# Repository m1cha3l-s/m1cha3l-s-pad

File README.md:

# m1cha3l's pad

My take on a macropad but with comfort added. Featuring 4x custom mapable MX-Style switches, 1x Rotary encoder and a 0.91 inch OLED display.

The pad runs KMK Firmware on a Seeed XIAO RP2040. For easy configuration it has been done with POG Configurator for easy setup and reconfiguration. QMK firmware will come in the future to make use of the OLED display.

The current firmware can be found in the m1cha3l folder

# IMPORTANT NOTES

You need to have CircuitPython installed on your board. [Here](https://learn.adafruit.com/welcome-to-circuitpython/installing-circuitpython)'s a guide. After you put the insides of m1cha3l in production or m1cha3l onto the board, or you use [POG](https://pog.heaper.de) to flash and customize.

As of right now the leds and OLED are not yet set up and firmware not yet 100% tested as I don't have the hardware, once I get it I will update it.

To balance the weight you HAVE to put few washers in the bottom part and secure them with hot glue.

You first have to put the switches in the top part, then solder the OLED to the PCB, then you can solder the switches and click them into the bottom part of the case.

The rotary encoder isn't mounted on the PCB due to size savings and also because I wanted to try something new. You can connect it with female jumper cable through the header on the back of the PCB. Also it doesn't have a cap on because I dont like the feeling of them and something just makes me happy seeing raw hardware.

# Looks of the pad

# CAD (Case)

The case uses a screwless design.

# Schematic/PCB

# Hardware used

| Part Name | Quantity |
|---|---:|
| 3D Printed case | 1 |
| Seeed XIAO RP2040 | 1 |
| EC11 Rotary encoders | 1 |
| MX-Style Switch | 4 |
| Keycap | 4 |
| SK6812MINI-E | 4 |
| Custom PCB | 1 |
| Old/washers | 4 |

# My feelings

Love the project from start to finish and it helped me learn a lot of things and guide me to get my first shipped project! I highly suggest you try and build the macropad from scratch yourself as it is easy to understand and teaches you the basics.

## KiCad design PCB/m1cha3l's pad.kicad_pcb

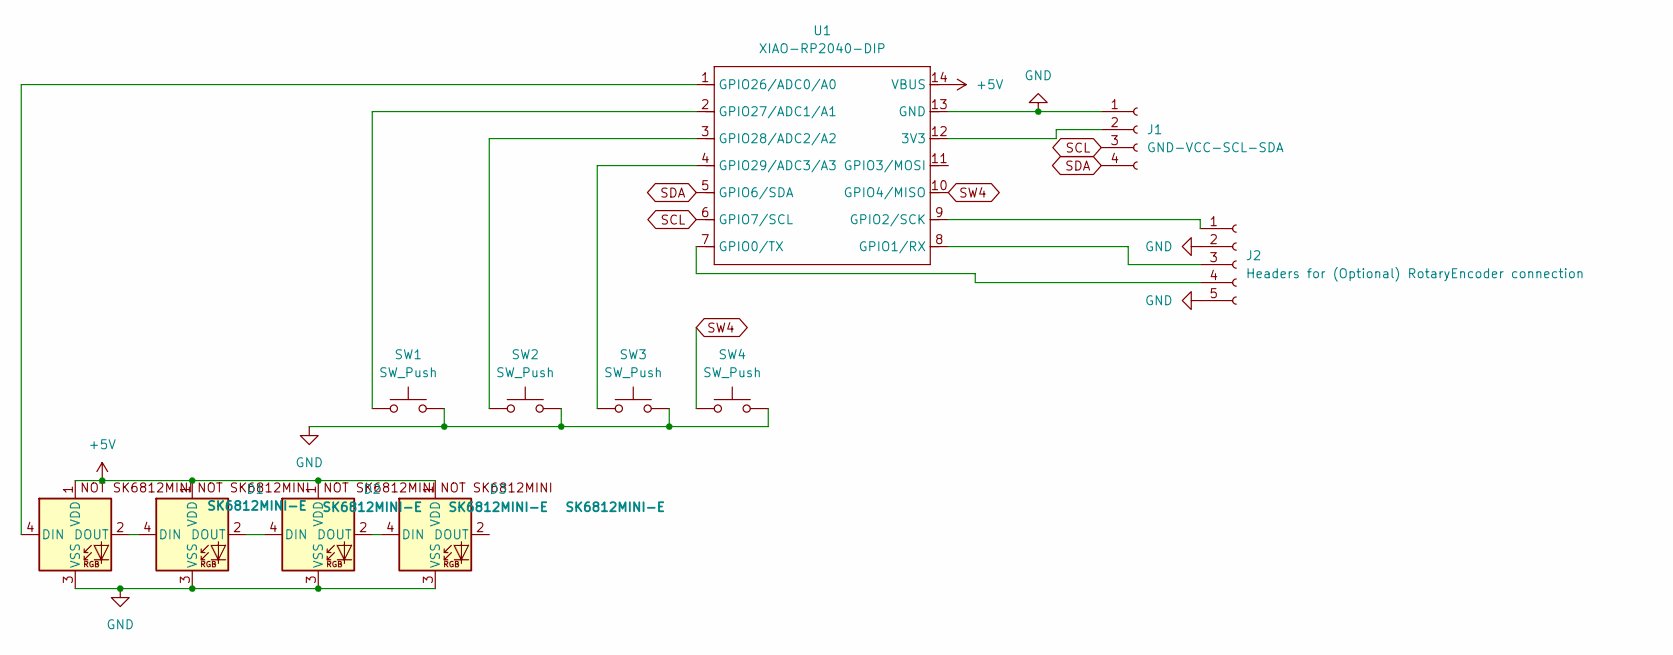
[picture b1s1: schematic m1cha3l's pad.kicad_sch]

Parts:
D1, D2, D3, D4: SK6812MINI-E; SK6812MINI-E_fixed
J1: GND-VCC-SCL-SDA; SSD1306-0.91-OLED-4pin-128x32
J2: Headers for (Optional) RotaryEncoder connection; PinHeader_1x05_P2.54mm_Vertical
SW1, SW2, SW3, SW4: SW_Push; SW_Cherry_MX_1.00u_PCB
U1: XIAO-RP2040-DIP

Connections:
+5V: D1.1 (VDD), D2.1 (VDD), D3.1 (VDD), D4.1 (VDD), U1.14 (VBUS)
GND: D1.3 (VSS), D2.3 (VSS), D3.3 (VSS), D4.3 (VSS), J1.1, J2.2, J2.5, SW1.2, SW2.2, SW3.2, SW4.2, U1.13 (GND)
unnamed: D1.4 (DIN), U1.1 (GPIO26/ADC0/A0)
unnamed: D1.2 (DOUT), D2.4 (DIN)
unnamed: D2.2 (DOUT), D3.4 (DIN)
unnamed: D3.2 (DOUT), D4.4 (DIN)
unnamed: J1.2, U1.12 (3V3)
unnamed: J2.1, U1.9 (GPIO2/SCK)
unnamed: J2.3, U1.8 (GPIO1/RX)
unnamed: J2.4, U1.7 (GPIO0/TX)
unnamed: SW1.1, U1.2 (GPIO27/ADC1/A1)
unnamed: SW2.1, U1.3 (GPIO28/ADC2/A2)
unnamed: SW3.1, U1.4 (GPIO29/ADC3/A3)
SCL: J1.3, U1.6 (GPIO7/SCL)
SDA: J1.4, U1.5 (GPIO6/SDA)
SW4: SW4.1, U1.10 (GPIO4/MISO)

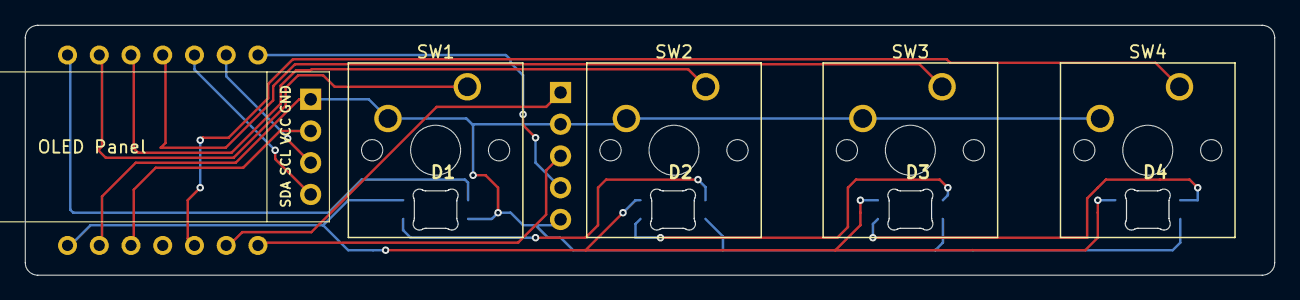
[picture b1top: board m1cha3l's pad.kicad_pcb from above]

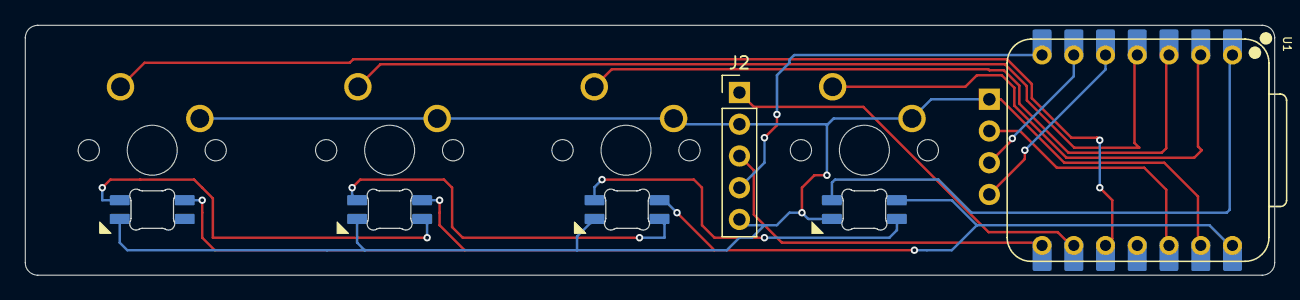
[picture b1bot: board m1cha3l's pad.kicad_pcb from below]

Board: 2 copper layers, 100.0 x 20.0 mm, 11 parts (2 on the bottom side), 16 nets.

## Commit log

2026-02-23 Create cad
2026-02-23 Uploaded CAD files for case
2026-02-23 Create pcb
2026-02-23 Create firmware
2026-02-23 Create production
2026-02-23 CAD files for printing
2026-02-23 Gerber for JLCPCB
2026-02-23 Create pic
2026-02-25 Updated gerbers with new PCB connection
2026-02-25 Changed SW4 and OLED connection
2026-03-19 Initial plan
2026-03-19 Add QMK firmware for m1cha3l's pad (RP2040, OLED, RGB, encoder)
2026-03-20 Fix formatting in README.md
